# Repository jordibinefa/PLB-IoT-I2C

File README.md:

# PLB-IoT-I2C
Programming Learning Board - Internet of Things - Inter Integrated Circuit (KiCAD files)

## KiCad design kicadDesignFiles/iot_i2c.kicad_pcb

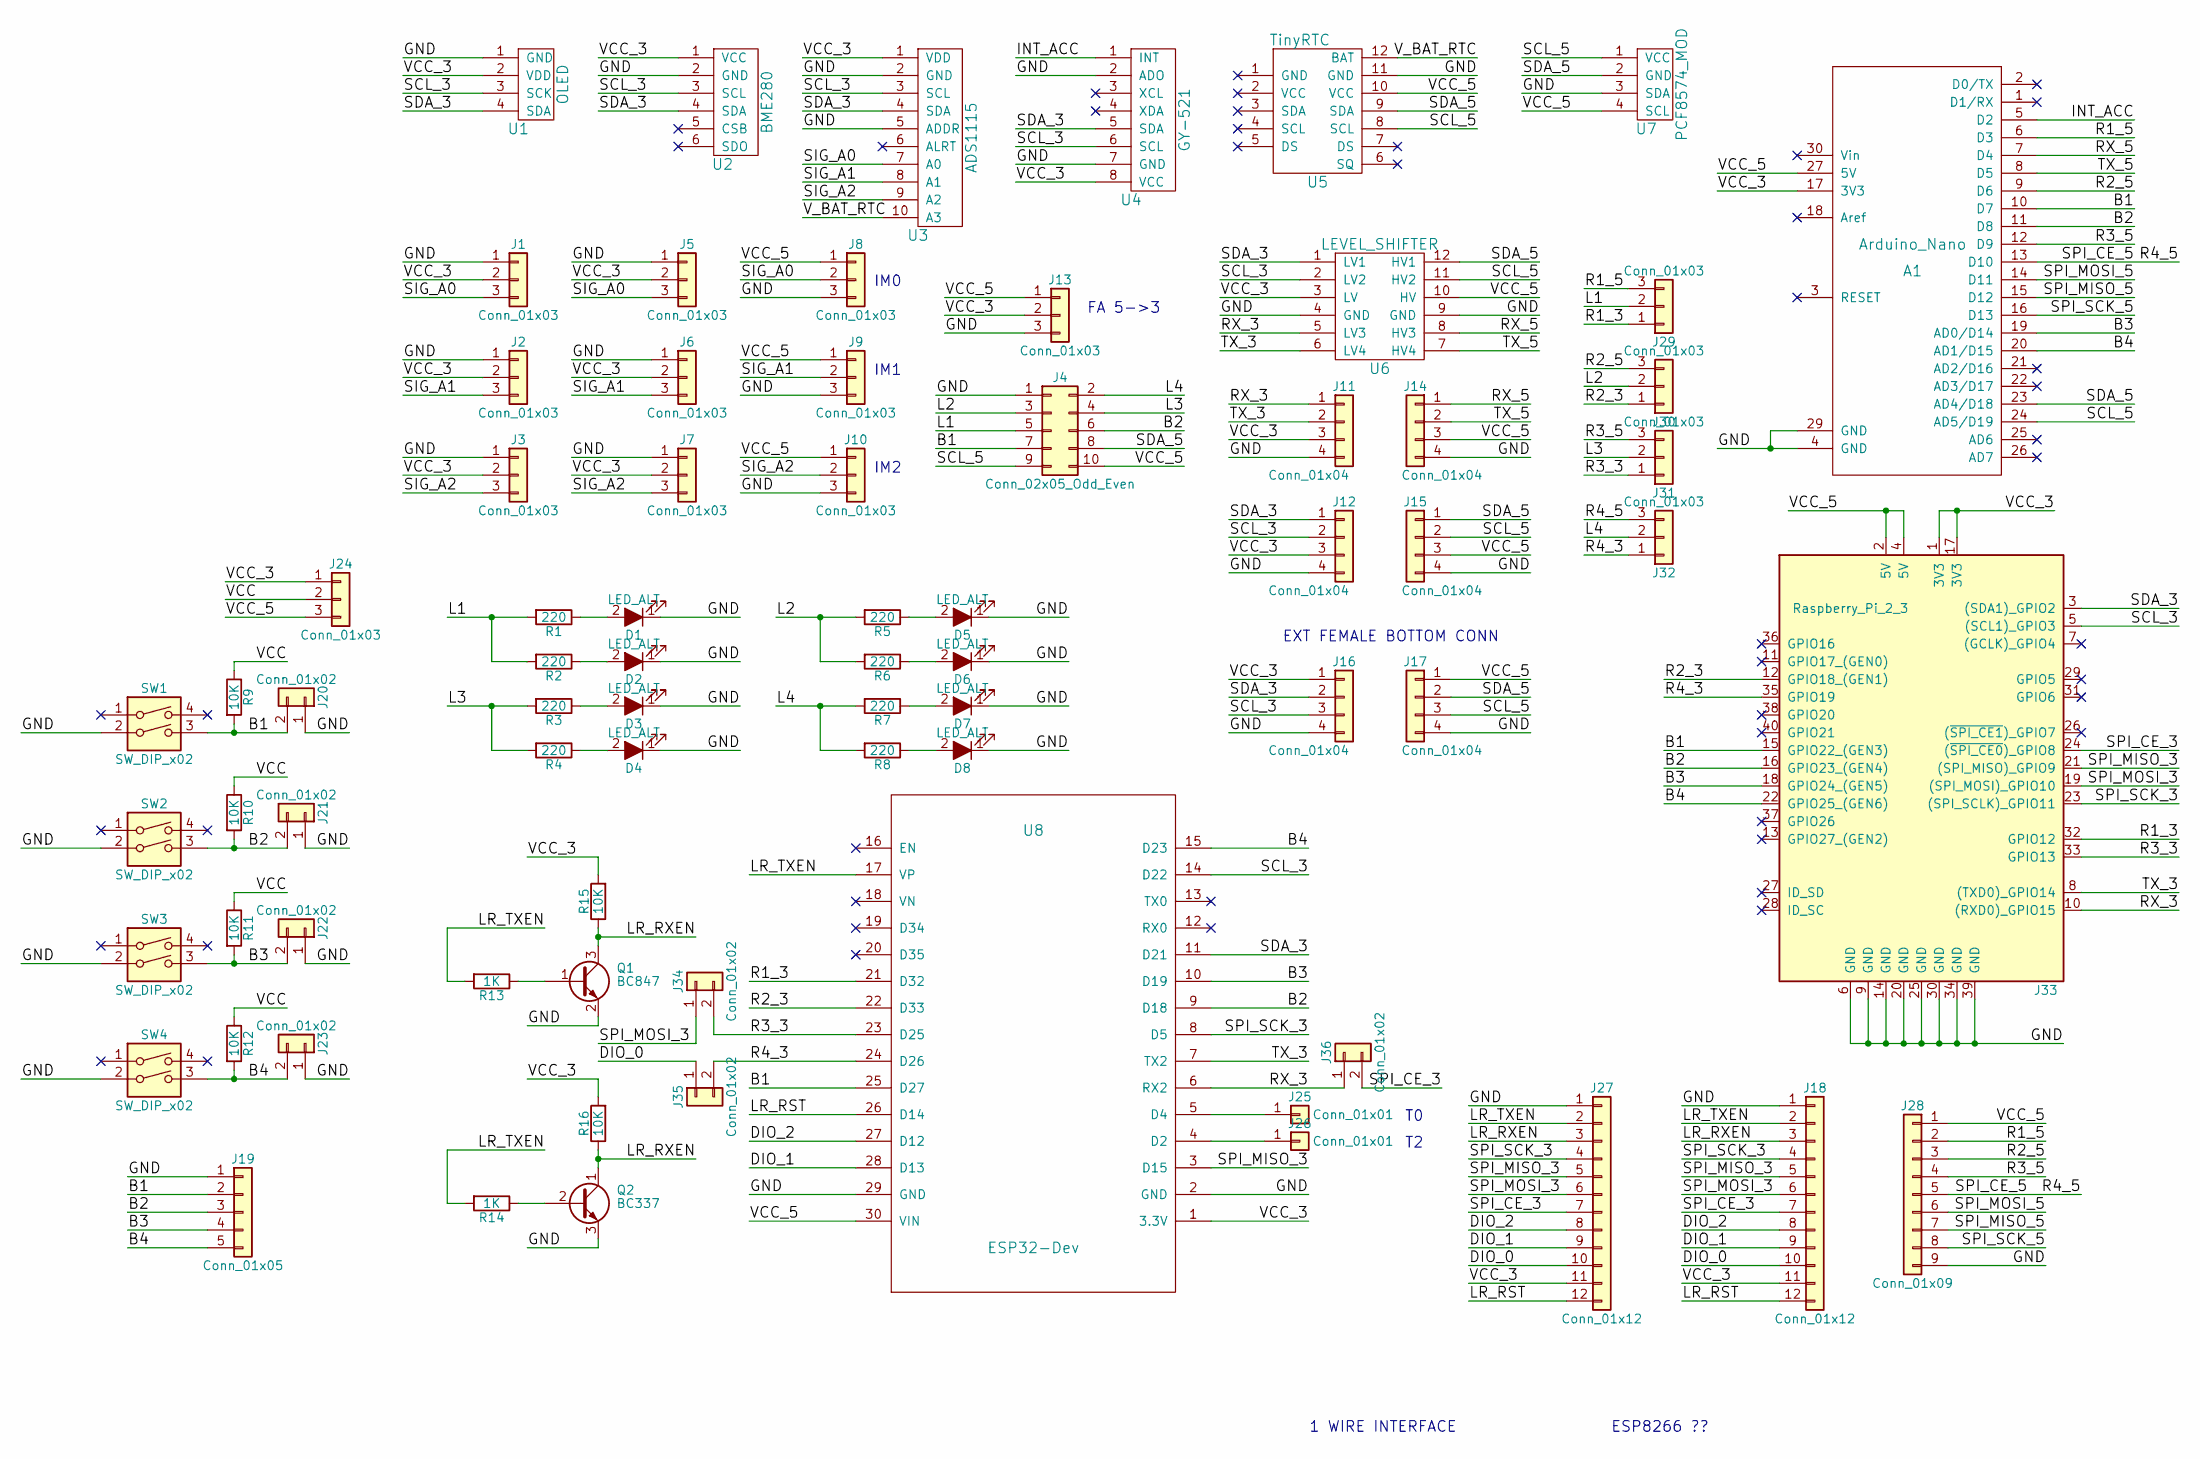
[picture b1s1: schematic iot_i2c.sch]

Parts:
A1: Arduino_Nano; ARDUINO_NANO
D1, D3, D5, D7: LED_ALT; SMD-1206_Pol
D2, D4, D6, D8: LED_ALT; LED_D5.0mm_FlatTop
J1, J2, J3: Conn_01x03; Socket_Strip_Angled_1x03_Pitch2.54mm
J4: Conn_02x05_Odd_Even; CONN_5_eCAT
J5, J6, J7, J24, J29, J30, J31, J32: Conn_01x03; Pin_Header_Straight_1x03_Pitch2.54mm
J8, J9, J10, J13: Conn_01x03; Socket_Strip_Straight_1x03_Pitch2.54mm
J11, J12, J14, J15: Conn_01x04; Pin_Header_Straight_1x04_Pitch2.54mm
J16, J17: Conn_01x04; Socket_Strip_Straight_1x04_Pitch2.54mm
J18: Conn_01x12; Pin_Header_Straight_1x12_Pitch2.54mm
J19: Conn_01x05; Pin_Header_Straight_1x05_Pitch2.54mm
J20, J21, J22, J23, J34, J35, J36: Conn_01x02; Pin_Header_Straight_1x02_Pitch2.54mm
J25, J26: Conn_01x01; Pin_Header_Straight_1x01_Pitch2.54mm
J27: Conn_01x12; Socket_Strip_Straight_1x12_Pitch2.54mm
J28: Conn_01x09; Pin_Header_Straight_1x09_Pitch2.54mm
J33: Raspberry_Pi_2_3; Socket_Strip_Straight_2x20_Pitch2.54mm
Q1: BC847; SOT-23
Q2: BC337; TO-92_Molded_Narrow
R1, R3, R5, R7: 220; R_0805_HandSoldering
R2, R4, R6, R8: 220; RESISTENCIA_0.25W
R9, R10, R11, R12, R15: 10K; R_0805_HandSoldering
R13: 1K; R_0805_HandSoldering
R14: 1K; RESISTENCIA_0.25W
R16: 10K; RESISTENCIA_0.25W
SW1, SW2, SW3, SW4: SW_DIP_x02; BUTTON_THROUGH_HOLE
U1: OLED; Socket_Strip_Straight_1x04_Pitch2.54mm
U2: BME280
U3: ADS1115; Socket_Strip_Straight_1x10_Pitch2.54mm
U4: GY-521; Socket_Strip_Straight_1x08_Pitch2.54mm
U5: TinyRTC
U6: LEVEL_SHIFTER
U7: PCF8574_MOD; Socket_Strip_Angled_1x04_Pitch2.54mm
U8: ESP32-Dev; ESP32_DEVKIT_V1

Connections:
/B1: A1.10 (D7), J4.7, J19.2, J20.2, J33.15 (GPIO22_(GEN3)), R9.2, SW1.3, U8.25 (D27)
/B2: A1.11 (D8), J4.6, J19.3, J21.2, J33.16 (GPIO23_(GEN4)), R10.2, SW2.3, U8.9 (D18)
/B3: A1.19 (AD0/D14), J19.4, J22.2, J33.18 (GPIO24_(GEN5)), R11.2, SW3.3, U8.10 (D19)
/B4: A1.20 (AD1/D15), J19.5, J23.2, J33.22 (GPIO25_(GEN6)), R12.2, SW4.3, U8.15 (D23)
/DIO_0: J18.10, J27.10, J35.1
/DIO_1: J18.9, J27.9, U8.28 (D13)
/DIO_2: J18.8, J27.8, U8.27 (D12)
/GND: A1.4 (GND), A1.29 (GND), D1.1 (K), D2.1 (K), D3.1 (K), D4.1 (K), D5.1 (K), D6.1 (K), D7.1 (K), D8.1 (K), J1.1, J2.1, J3.1, J4.1, J5.1, J6.1, J7.1, J8.3, J9.3, J10.3, J11.4, J12.4, J13.3, J14.4, J15.4, J16.4, J17.4, J18.1, J19.1, J20.1, J21.1, J22.1, J23.1, J27.1, J28.9, J33.6 (GND), J33.9 (GND), J33.14 (GND), J33.20 (GND), J33.25 (GND), J33.30 (GND), J33.34 (GND), J33.39 (GND), Q1.2 (E), Q2.3 (E), SW1.2, SW2.2, SW3.2, SW4.2, U1.1 (GND), U2.2 (GND), U3.2 (GND), U3.5 (ADDR), U4.2 (ADO), U4.7 (GND), U5.11 (GND), U6.4 (GND), U6.9 (GND), U7.3 (SDA), U8.2 (GND), U8.29 (GND)
/INT_ACC: A1.5 (D2), U4.1 (INT)
/L1: J4.5, J29.2, R1.2, R2.2
/L2: J4.3, J30.2, R5.2, R6.2
/L3: J4.4, J31.2, R3.2, R4.2
/L4: J4.2, J32.2, R7.2, R8.2
/LR_RST: J18.12, J27.12, U8.26 (D14)
/LR_RXEN: J18.3, J27.3, Q1.3 (C), Q2.1 (C), R15.1, R16.1
/LR_TXEN: J18.2, J27.2, R13.2, R14.2, U8.17 (VP)
/R1_3: J29.1, J33.32 (GPIO12), U8.21 (D32)
/R1_5: A1.6 (D3), J28.2, J29.3
/R2_3: J30.1, J33.12 (GPIO18_(GEN1)), U8.22 (D33)
/R2_5: A1.9 (D6), J28.3, J30.3
/R3_3: J31.1, J33.33 (GPIO13), J34.2, U8.23 (D25)
/R3_5: A1.12 (D9), J28.4, J31.3
/R4_3: J32.1, J33.35 (GPIO19), J35.2, U8.24 (D26)
/R4_5: A1.13 (D10), J28.5, J32.3
/RX_3: J11.1, J33.10 ((RXD0)_GPIO15), J36.1, U6.5 (LV3), U8.6 (RX2)
/RX_5: A1.7 (D4), J14.1, U6.8 (HV3)
/SCL_3: J12.2, J16.3, J33.5 ((SCL1)_GPIO3), U1.3 (SCK), U2.3 (SCL), U3.3 (SCL), U4.6 (SCL), U6.2 (LV2), U8.14 (D22)
/SCL_5: A1.24 (AD5/D19), J4.9, J15.2, J17.3, U5.8 (SCL), U6.11 (HV2), U7.1 (VCC)
/SDA_3: J12.1, J16.2, J33.3 ((SDA1)_GPIO2), U1.4 (SDA), U2.4 (SDA), U3.4 (SDA), U4.5 (SDA), U6.1 (LV1), U8.11 (D21)
/SDA_5: A1.23 (AD4/D18), J4.8, J15.1, J17.2, U5.9 (SDA), U6.12 (HV1), U7.2 (GND)
/SIG_A0: J1.3, J5.3, J8.2, U3.7 (A0)
/SIG_A1: J2.3, J6.3, J9.2, U3.8 (A1)
/SIG_A2: J3.3, J7.3, J10.2, U3.9 (A2)
/SPI_CE_3: J18.7, J27.7, J33.24 ((~SPI_CE0~)_GPIO8), J36.2
/SPI_MISO_3: J18.5, J27.5, J33.21 ((SPI_MISO)_GPIO9), U8.3 (D15)
/SPI_MISO_5: A1.15 (D12), J28.7
/SPI_MOSI_3: J18.6, J27.6, J33.19 ((SPI_MOSI)_GPIO10), J34.1
/SPI_MOSI_5: A1.14 (D11), J28.6
/SPI_SCK_3: J18.4, J27.4, J33.23 ((SPI_SCLK)_GPIO11), U8.8 (D5)
/SPI_SCK_5: A1.16 (D13), J28.8
/TX_3: J11.2, J33.8 ((TXD0)_GPIO14), U6.6 (LV4), U8.7 (TX2)
/TX_5: A1.8 (D5), J14.2, U6.7 (HV4)
/VCC: J24.2, R9.1, R10.1, R11.1, R12.1
/VCC_3: A1.17 (3V3), J1.2, J2.2, J3.2, J5.2, J6.2, J7.2, J11.3, J12.3, J13.2, J16.1, J18.11, J24.1, J27.11, J33.1 (3V3), J33.17 (3V3), R15.2, R16.2, U1.2 (VDD), U2.1 (VCC), U3.1 (VDD), U4.8 (VCC), U6.3 (LV), U8.1 (3.3V)
/VCC_5: A1.27 (5V), J4.10, J8.1, J9.1, J10.1, J13.1, J14.3, J15.3, J17.1, J24.3, J28.1, J33.2 (5V), J33.4 (5V), U5.10 (VCC), U6.10 (HV), U7.4 (SCL), U8.30 (VIN)
/V_BAT_RTC: U3.10 (A3), U5.12 (BAT)
unnamed: D1.2 (A), R1.1
unnamed: D2.2 (A), R2.1
unnamed: D3.2 (A), R3.1
unnamed: D4.2 (A), R4.1
unnamed: D5.2 (A), R5.1
unnamed: D6.2 (A), R6.1
unnamed: D7.2 (A), R7.1
unnamed: D8.2 (A), R8.1
unnamed: J25.1, U8.5 (D4)
unnamed: J26.1, U8.4 (D2)
unnamed: Q1.1 (B), R13.1
unnamed: Q2.2 (B), R14.1

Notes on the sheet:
FA 5->3
IM0
IM1
IM2
EXT FEMALE BOTTOM CONN
1 WIRE INTERFACE
ESP8266 ??

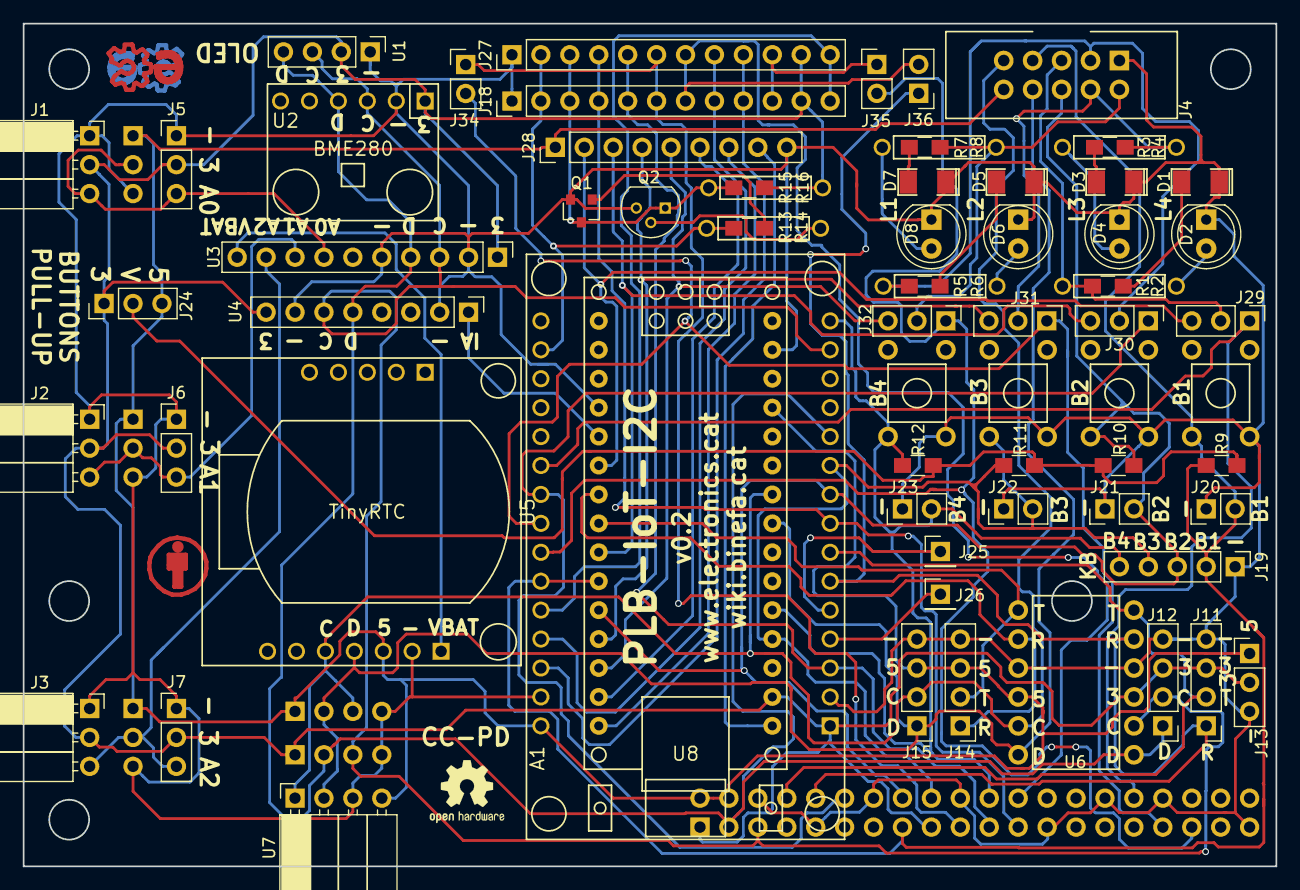
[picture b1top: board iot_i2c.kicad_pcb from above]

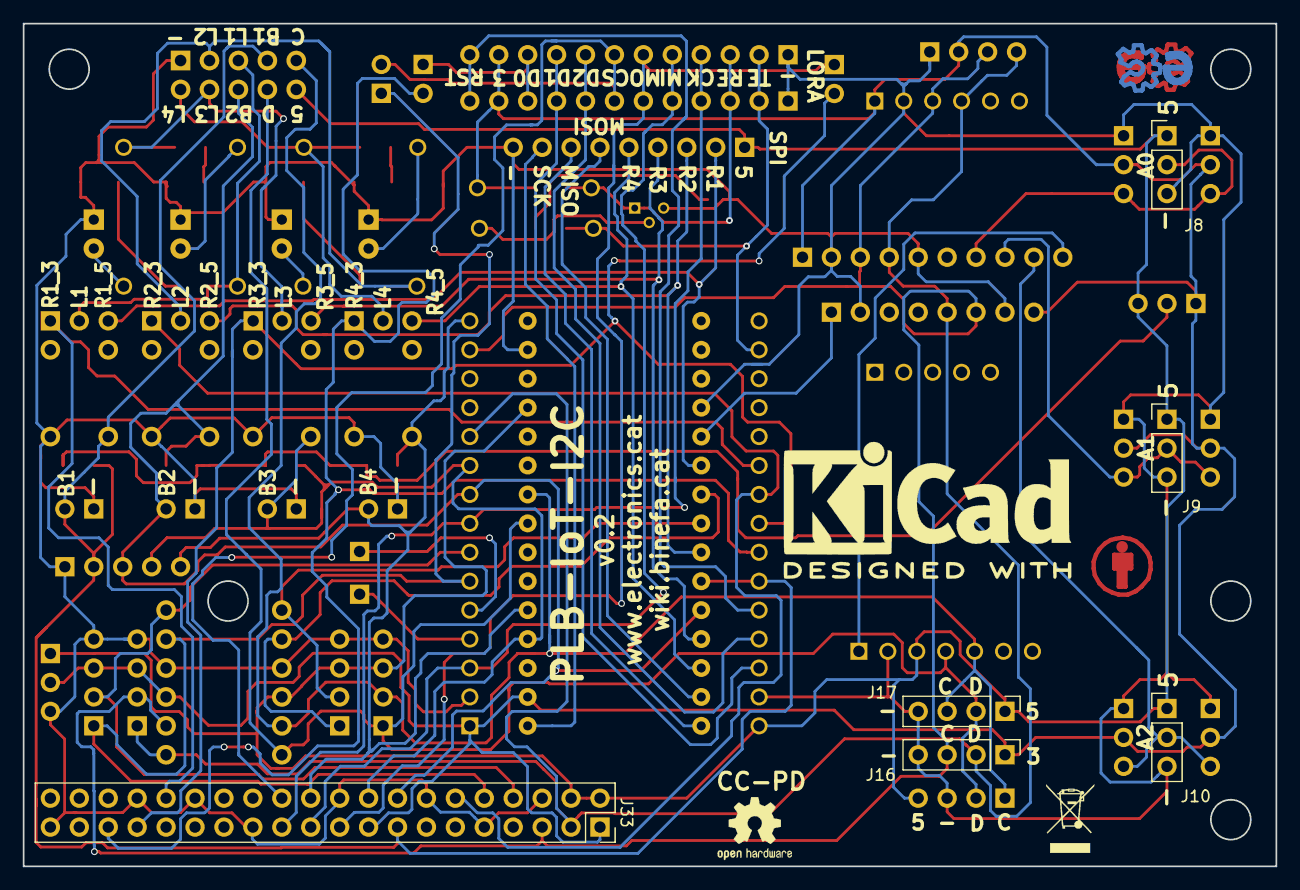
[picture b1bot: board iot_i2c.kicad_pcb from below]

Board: 2 copper layers, 110.0 x 74.0 mm, 77 parts (7 on the bottom side), 58 nets.

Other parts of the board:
VAL: logo_eCat
VAL#2: logo_eCat
